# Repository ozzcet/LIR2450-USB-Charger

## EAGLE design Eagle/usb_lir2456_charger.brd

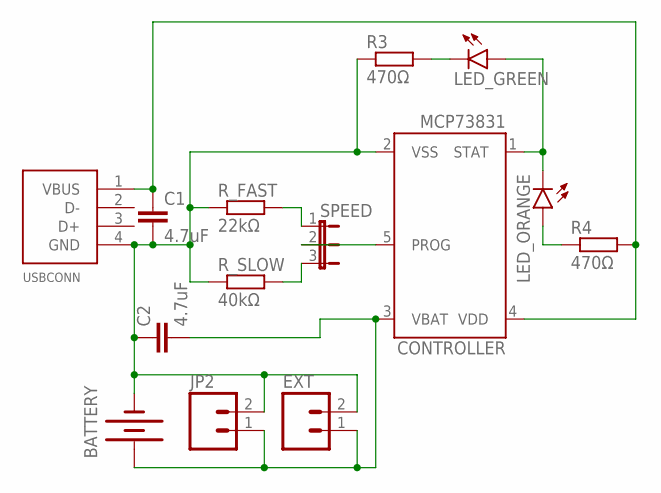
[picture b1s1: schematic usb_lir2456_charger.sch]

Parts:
BATTERY: BATTERY20PTH; BATTCOM_20MM_PTH
C1, C2: 4.7uF; C0805
CONTROLLER: MCP73831; SOT23-5
EXT: M02PTH; 1X02
JP2: M02JST-PTH-VERT; JST-2-PTH-VERT
LED_GREEN: LED0603; LED-0603
LED_ORANGE: LED0603; LED-0603
R3, R4: 470Ω; R0805
R_FAST: 22kΩ; R0805
R_SLOW: 40kΩ; R0805
SPEED: JP2E; JP2
USBCONN: USB-CON-4PIN; USB-MALE-A-PCB

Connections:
GND: BATTERY.2 (-), C1.2, C2.1, CONTROLLER.2 (VSS), EXT.2, JP2.2, R3.1, R_FAST.1, R_SLOW.1, USBCONN.4 (GND)
unnamed: CONTROLLER.1 (STAT), LED_GREEN.A, LED_ORANGE.C
unnamed: CONTROLLER.5 (PROG), SPEED.2
unnamed: LED_GREEN.C, R3.2
unnamed: R_SLOW.2, SPEED.3
unnamed: R_FAST.2, SPEED.1
unnamed: LED_ORANGE.A, R4.1
unnamed: BATTERY.1 (+), C2.2, CONTROLLER.3 (VBAT), EXT.1, JP2.1
VCC: C1.1, CONTROLLER.4 (VDD), R4.2, USBCONN.1 (VBUS)

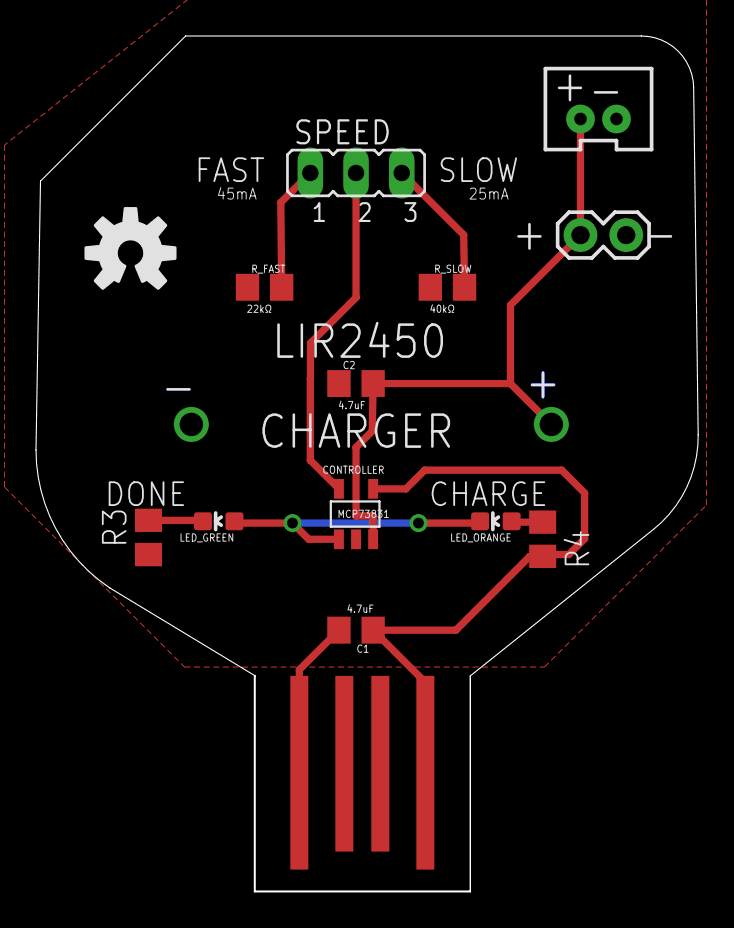
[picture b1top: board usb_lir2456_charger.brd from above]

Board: 2 copper layers, 36.8 x 47.5 mm, 15 parts (1 on the bottom side), 9 nets.

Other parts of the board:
U$1: OSHW-LOGO-M

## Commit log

2021-02-28 Edited Charge and Done Led connections
    actually I have not able to test it is it correct or not. How ever next week i will be able to do it. Before it maybe some one could have chance before me. Best regards. Note: I have get the idea fro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

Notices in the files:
parts and their libraries:
GeekAmmo: Licensing:Creative Commons ShareAlike 4.0 International - https://creativecommons.org/licenses/by-sa/4.0
